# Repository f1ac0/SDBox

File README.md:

# SDBox
The SDBox project by jbilander and based on the SPI adapter by niklasekstrom is a wonderful parallel sdcard reader for Amiga computers. Thank you guys for sharing it under GPLv3 license.
https://github.com/jbilander/sdbox

I use it to transfer files either to my A500 with internal IDE adapter or to my A600 or 1200 without blocking the PCMCIA port.

The project in this repository is just a recreated board making use of the bare chips instead of breadboard modules.
- It is smaller
- It accommodates big SD cards instead of microSD
- It takes its power from a Mini or Micro USB or from a pin header (I also use this header as an output to power a serial adapter using the same power pack)
- It does not include the 2nd LED and power switch
- It uses SMD stuff (maybe harder to solder)
- It is also designed using the KiCAD EDA

I guess it is not better than the original, just different for those who prefer tiny stuff.

For the software part, it works with the original firmware and driver.

# Disclaimer
This is a hobbyist project, it comes with no warranty and no support. Also remember that the Amiga machines are about 30 years old and may fail because of such hardware expansions.

This version is not endorsed by the original authors, please don't bother them with issues you might have because of it.

I publish this work using the same license as the original : GPLv3.

If you find it useful, please reward the original authors.

# BOM
- 1x Male DB25 header
- 1x SDCARD socket (SDP11-4-12B on the schematic I have but known with other names online)
- 1x ATMEGA 328p-au
- 1x SPX3819M5-L-3-3 3.3v LDO
- 1x 16MHz HC-49S crystal
- 2x 1uF (or more) 0805 capacitors
- 3x 100nF 0805 capacitors
- 2x 22pf 0805 capacitors
- 1x 4.7K 0805 resistor
- 1x 6.8K 0603x4 resistor array
- 1x 4.7K 0603x4 resistor array
- 1x optional 0805 LED and 0805 resistor (330 ohm or more)
For power, install the one you need :
- 1x Mini USB Female Socket 4 foot
- 1x Micro USB Female Socket B type 4.85 horn connector
- 1x 1x2 2.54mm pin header

# Making it
I recommend 1.6mm PCB since it is sandwiched between the pins of the DB25 connector.

Check for shorts at least between 5V, 3.3V, and GND traces before applying power !

The programming port does not need to be soldered since it needs to be programmed just once : you can just hold it in place during the few seconds required for programming.

The blank 328p chip needs to be programmed using its SPI port : for example connect an arduino as ISP, https://www.instructables.com/Burn-a-New-Bootloader-Arduino-Pro-Mini/
```
Arduino ------------------- this board
5V (VCC) ------------------ +5V
GND ----------------------- GND
Pin 10 -------------------- RST
Pin 11 -------------------- MOSI
Pin 12 -------------------- MISO
Pin 13 -------------------- SCK
```

Then to program the SDBox firmware on the 328p :
```
~/arduino/hardware/tools/avr/bin/avrdude -C ~/arduino/hardware/tools/avr/etc/avrdude.conf -v -patmega328p -cavrisp -P/dev/ttyUSB0 -b19200 -D -Uflash:w:main.hex:i
```

Alternatively, you may first program an arduino bootloader using the arduino IDE. Then you will be able to later program and update the SDBox firmware through UART TX and RX pins using a USB to serial adapter with :
```
~/arduino/hardware/tools/avr/bin/avrdude -C ~/arduino/hardware/tools/avr/etc/avrdude.conf -v -patmega328p -carduino -P/dev/ttyUSB0 -b57600 -D -Uflash:w:main.hex:i
```

# Using it
- Plug it to the parallel port
- Plug it to power block
- Insert SDcard
- Apply power
- Turn Amiga on
- Install the drivers
- Mount the sdcard using
```
mount devs:SD0
```
- Unmount the sdcard using
```
assign SD0: DISMOUNT
```
replace DISMOUNT with REMOVE on Kickstart 1.3.

If you care about your Amiga, this is a bad idea to plug or unplug the parallel port while live.

If you care about the data on the card or the card itself, it might also be a bad idea to plug or unplug it while power is applied. I personally have done so several times already without problem so far, just dismount the partition before unplugging.

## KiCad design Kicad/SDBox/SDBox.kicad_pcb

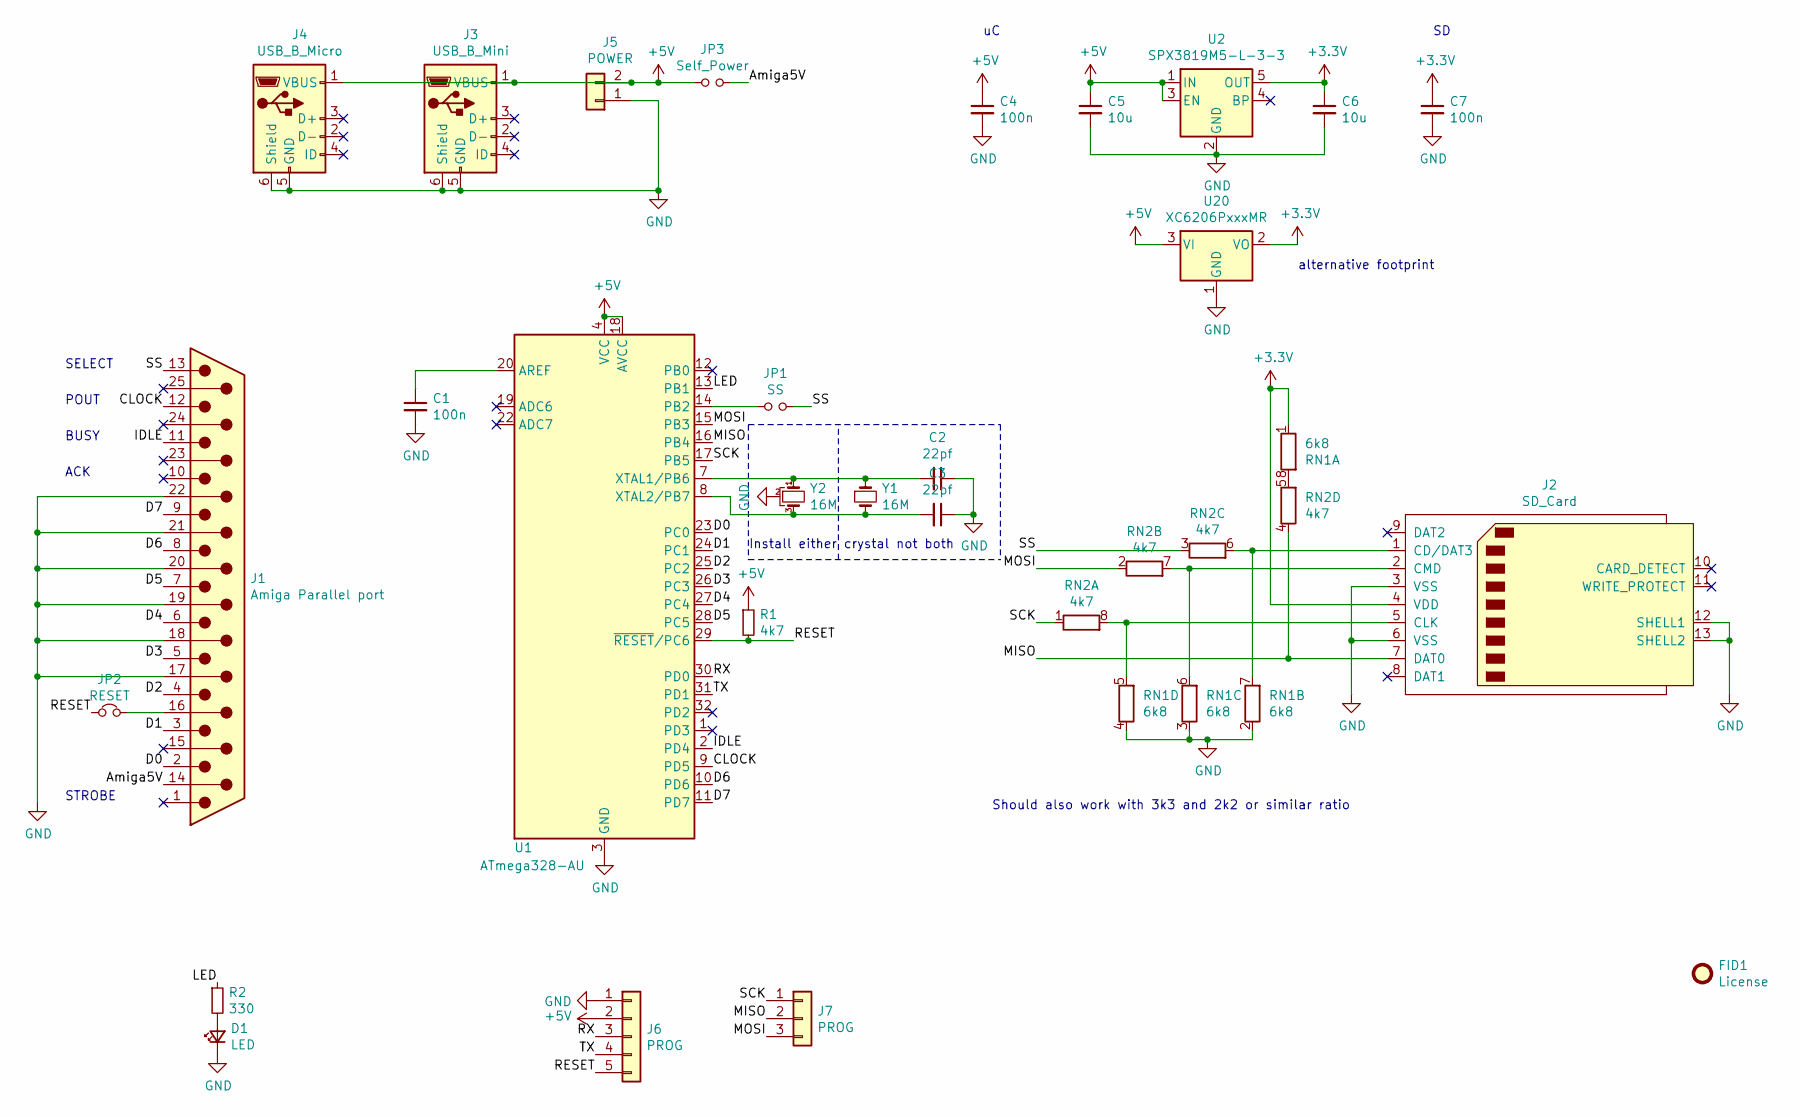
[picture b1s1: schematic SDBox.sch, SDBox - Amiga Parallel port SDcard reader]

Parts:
C1, C4, C7: 100n; C_0805_2012Metric
C2, C3: 22pf; C_0805_2012Metric
C5, C6: 10u; C_0805_2012Metric
D1: LED; LED_0805_2012Metric
FID1: License; OSHW-Logo2_7.3x6mm_SilkScreen
J1: Amiga Parallel port; DSUB-25_Male_EdgeMount_P2.77mm
J2: SD_Card; Conn_SDcard
J3: USB_B_Mini; USB_Mini-B_Lumberg_2486_01_Horizontal
J4: USB_B_Micro; USB_Micro-B_Molex-105017-0001
J5: POWER; PinHeader_1x02_P2.54mm_Vertical
J6: PROG; PinHeader_1x05_P2.54mm_Vertical
J7: PROG; PinHeader_1x03_P2.54mm_Vertical
JP1: SS; SolderJumper-2_P1.3mm_Open_RoundedPad1.0x1.5mm
JP2: RESET; SolderJumper-2_P1.3mm_Bridged_RoundedPad1.0x1.5mm
JP3: Self_Power; SolderJumper-2_P1.3mm_Open_RoundedPad1.0x1.5mm
R1: 4k7; R_0805_2012Metric
R2: 330; R_0805_2012Metric
RN1: 6k8; R_Array_Convex_4x0603
RN2: 4k7; R_Array_Convex_4x0603
U1: ATmega328-AU; TQFP-32_7x7mm_P0.8mm
U2: SPX3819M5-L-3-3; SOT-23-5
U20: XC6206PxxxMR; SOT-23
Y1: 16M; Crystal_SMD_HC49-SD
Y2: 16M; MURATA_CSTCE

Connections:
+3V3: C6.1, C7.1, J2.4 (VDD), RN1.1 (R1.1), U2.5 (OUT), U20.2 (VO)
+5V: C4.1, C5.1, J3.1 (VBUS), J4.1 (VBUS), J5.2, J6.2, JP3.1, R1.1, U1.4 (VCC), U1.6 (VCC), U1.18 (AVCC), U2.1 (IN), U2.3 (EN), U20.3 (VI)
/Amiga5V: J1.14, JP3.2
/CLOCK: J1.12, U1.9 (PD5)
/D0: J1.2, U1.23 (PC0)
/D1: J1.3, U1.24 (PC1)
/D2: J1.4, U1.25 (PC2)
/D3: J1.5, U1.26 (PC3)
/D4: J1.6, U1.27 (PC4)
/D5: J1.7, U1.28 (PC5)
/D6: J1.8, U1.10 (PD6)
/D7: J1.9, U1.11 (PD7)
/IDLE: J1.11, U1.2 (PD4)
/LED: R2.1, U1.13 (PB1)
/MISO: J2.7 (DAT0), J7.2, RN2.4 (R4.1), U1.16 (PB4)
/MOSI: J7.3, RN2.2 (R2.1), U1.15 (PB3)
/RESET: J6.5, JP2.1, R1.2, U1.29 (~RESET~/PC6)
/RX: J6.3, U1.30 (PD0)
/SCK: J7.1, RN2.1 (R1.1), U1.17 (PB5)
/SS: J1.13, JP1.2, RN2.3 (R3.1)
/TX: J6.4, U1.31 (PD1)
GND: C1.2, C2.1, C3.1, C4.2, C5.2, C6.2, C7.2, D1.1 (K), J1.17, J1.18, J1.19, J1.20, J1.21, J1.22, J2.3 (VSS), J2.6 (VSS), J2.12 (SHELL1), J2.13 (SHELL2), J3.5 (GND), J3.6 (Shield), J4.5 (GND), J4.6 (Shield), J5.1, J6.1, RN1.2 (R2.1), RN1.3 (R3.1), RN1.4 (R4.1), U1.3 (GND), U1.5 (GND), U1.21 (GND), U2.2 (GND), U20.1 (GND), Y2.2
unnamed: C1.1, U1.20 (AREF)
unnamed: C2.2, U1.7 (XTAL1/PB6), Y1.1, Y2.1
unnamed: C3.2, U1.8 (XTAL2/PB7), Y1.2, Y2.3
unnamed: D1.2 (A), R2.2
unnamed: J1.16, JP2.2
unnamed: J2.1 (CD/DAT3), RN1.7 (R2.2), RN2.6 (R3.2)
unnamed: J2.2 (CMD), RN1.6 (R3.2), RN2.7 (R2.2)
unnamed: J2.5 (CLK), RN1.5 (R4.2), RN2.8 (R1.2)
unnamed: JP1.1, U1.14 (PB2)
unnamed: RN1.8 (R1.2), RN2.5 (R4.2)

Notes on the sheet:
POUT
BUSY
Should also work with 3k3 and 2k2 or similar ratio
SELECT
ACK
STROBE
Install either crystal not both
alternative footprint

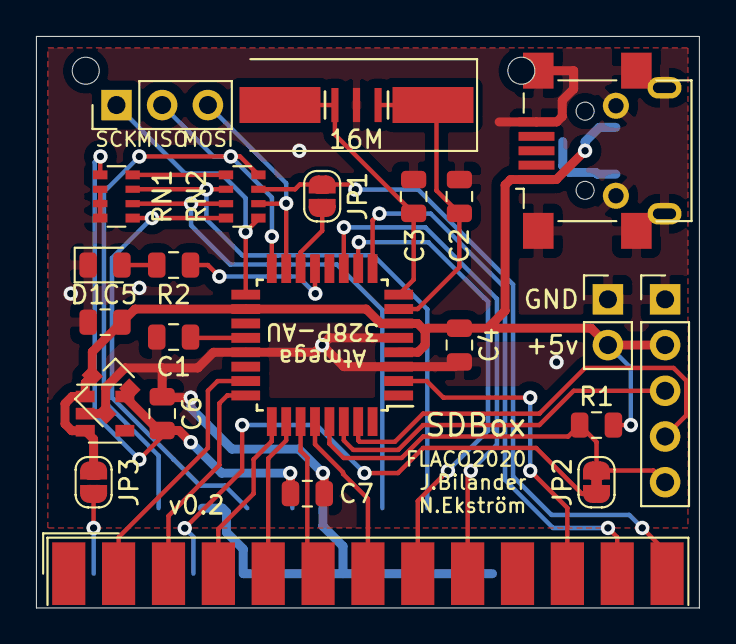
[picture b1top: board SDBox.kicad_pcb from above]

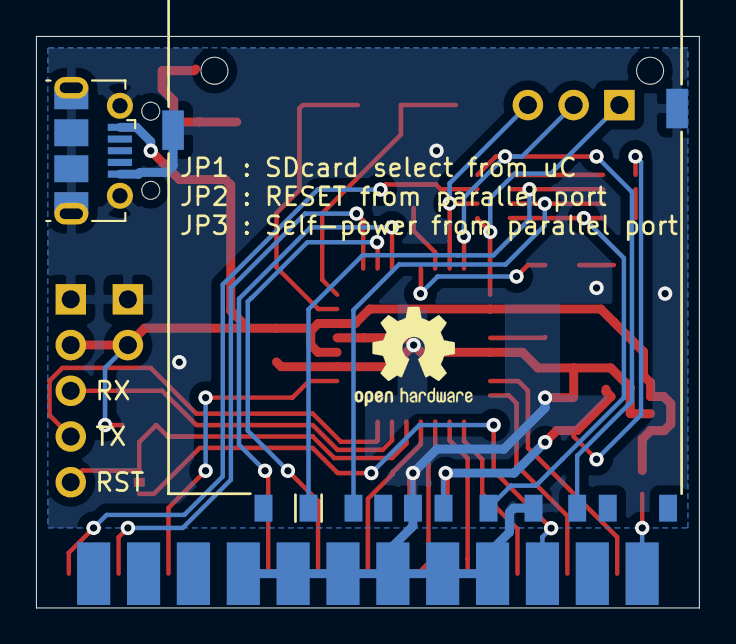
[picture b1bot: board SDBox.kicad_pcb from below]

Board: 2 copper layers, 36.8 x 31.8 mm, 28 parts (3 on the bottom side), 32 nets.

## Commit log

2020-07-30 Respository init with v0.1 KiCAD files, Readme and License
2020-07-30 Readme update
2020-09-23 Added CSTCE crystal footprint
2021-07-15 Kicad : 0.2 with broken SPI programming port
2022-02-15 Photo and InteractiveHtmlBom

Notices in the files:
Kicad/SDBox/SDBox.kicad_pcb:
Same license as original : GPL3.0 license on Gitbub but marked as OSHW on PCB
